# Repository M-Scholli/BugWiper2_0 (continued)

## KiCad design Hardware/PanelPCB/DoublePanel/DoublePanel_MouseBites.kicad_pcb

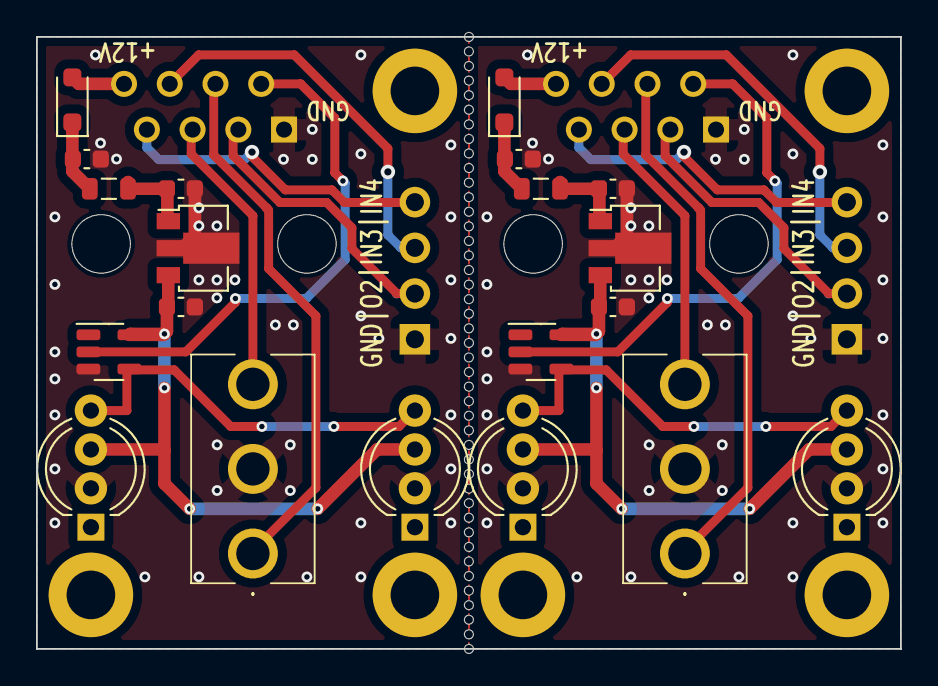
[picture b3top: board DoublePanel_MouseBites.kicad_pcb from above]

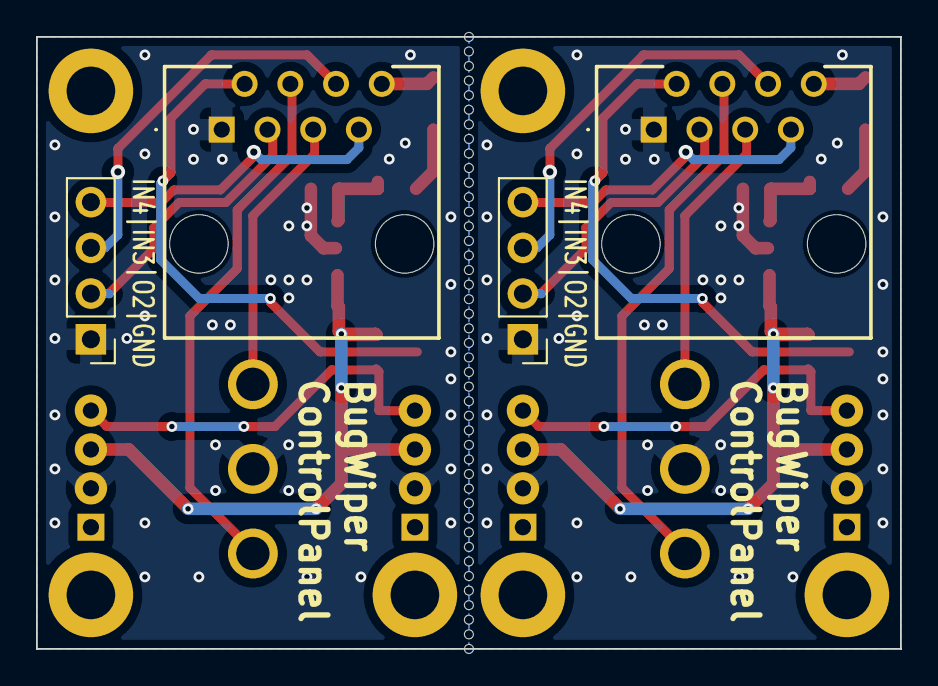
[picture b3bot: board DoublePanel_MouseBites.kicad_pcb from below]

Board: 2 copper layers, 48.0 x 34.0 mm, 73 parts (4 on the bottom side), 24 nets.

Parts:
C1, C1#2, C3, C3#2: 100nF; C_0603_1608Metric
C2, C2#2: 470nF; C_0603_1608Metric
D1, D1#2, D3, D3#2: APA-106-F5; LED_D5.0mm-4_RGB_Wide_Pins
D2, D2#2: CUS15S30,H3F; D_SOD-323_HandSoldering
H1, H1#2, H2, H2#2, H3, H3#2: MountingHole; MountingHole_2.7mm_M2.5_DIN965_Pad
J1, J1#2: RJ45; MJ3415882
J2, J2#2: Conn_01x03_Socket; PinHeader_1x04_P2.54mm_Vertical
KiKit_MB_1_1, KiKit_MB_1_2, KiKit_MB_1_3, KiKit_MB_1_4, KiKit_MB_1_5, KiKit_MB_1_6, KiKit_MB_1_7, KiKit_MB_1_8, KiKit_MB_1_9, KiKit_MB_1_10, KiKit_MB_1_11, KiKit_MB_1_12, KiKit_MB_1_13, KiKit_MB_1_14, KiKit_MB_1_15, KiKit_MB_1_16, KiKit_MB_1_17, KiKit_MB_1_18, KiKit_MB_1_19, KiKit_MB_1_20, KiKit_MB_1_21, KiKit_MB_1_22, KiKit_MB_1_23, KiKit_MB_1_24, KiKit_MB_1_25, KiKit_MB_1_26, KiKit_MB_1_27, KiKit_MB_1_28, KiKit_MB_1_29, KiKit_MB_1_30, KiKit_MB_1_31, KiKit_MB_1_32, KiKit_MB_1_33, KiKit_MB_1_34, KiKit_MB_1_35, KiKit_MB_1_36, KiKit_MB_1_37, KiKit_MB_1_38, KiKit_MB_1_39, KiKit_MB_1_40, KiKit_MB_1_41, KiKit_MB_1_42, KiKit_MB_1_43: NPTH
L1, L1#2: L_Ferrite; L_0805_2012Metric
S1, S1#2: 100SP4T1B4M2QE
U1, U1#2: AP2204R-5.0; SOT-89-3
U2, U2#2: SN74LV1T34DBV; SOT-23-5

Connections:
Board_0-+5V: C2#2.1, D1.3 (VDD), D3.3 (VDD), U1#2.3 (VOUT), U2#2.5 (VCC)
Board_0-GND1: C1#2.2, C2#2.2, C3.2, D1.2 (GND), D3.2 (GND), J1.1, J2.1, S1.2 (COM), U1#2.2 (GND), U2#2.3 (GND)
Board_0-IN1: J1.4, S1.1 (NO)
Board_0-IN2: J1.5, S1.3 (NO)
Board_0-IN3: J1.6, J2.3
Board_0-IN4: J1.7, J2.4
Board_0-Net-(D2-K): C3.1, D2#2.1 (K), L1#2.1
Board_0-Net-(U1-VIN): C1#2.1, L1#2.2, U1#2.1 (VIN)
Board_0-OUT1: J1.2, U2#2.2 (A)
Board_0-OUT2: J1.3, J2.2
Board_0-OUT_1: D1.4 (DI), D3.4 (DI), U2#2.4 (Y)
Board_0-V_IN: D2#2.2 (A), J1.8
Board_1-+5V: C2.1, D1#2.3 (VDD), D3#2.3 (VDD), U1.3 (VOUT), U2.5 (VCC)
Board_1-GND1: C1.2, C2.2, C3#2.2, D1#2.2 (GND), D3#2.2 (GND), J1#2.1, J2#2.1, S1#2.2 (COM), U1.2 (GND), U2.3 (GND)
Board_1-IN1: J1#2.4, S1#2.1 (NO)
Board_1-IN2: J1#2.5, S1#2.3 (NO)
Board_1-IN3: J1#2.6, J2#2.3
Board_1-IN4: J1#2.7, J2#2.4
Board_1-Net-(D2-K): C3#2.1, D2.1 (K), L1.1
Board_1-Net-(U1-VIN): C1.1, L1.2, U1.1 (VIN)
Board_1-OUT1: J1#2.2, U2.2 (A)
Board_1-OUT2: J1#2.3, J2#2.2
Board_1-OUT_1: D1#2.4 (DI), D3#2.4 (DI), U2.4 (Y)
Board_1-V_IN: D2.2 (A), J1#2.8

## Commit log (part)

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2016-07-02 Auskommentierter Code gelöscht
2016-07-02 Benutzung der Arduino PWM Befehle
2016-07-02 überflüssige Funktionen gelöscht und den Definitionsteil neu formatiert
2016-07-02 Sicherheit Taster ( SAVE_PIN) wird jetzt in der Main abgefragt und wird mit der Arduino Lib abgefragt.
2016-07-02 Formatierung und löschen unbenutzter Zeilen
2016-07-02 hinzufügen der Einstellungen von Eclipse
2016-07-02 motor_soft_a gelöscht, da überflüssig
2016-07-02 _delay_ms mit delay ersetzt
2016-07-02 Neue Entprellung ohne Verwendung von Timern oder Interrupts
2016-07-02 Struktur von putzen angepasst und den Lose Taster mit eingebunden
2016-07-04 Es reicht beim Starten die Richtung aus dem EEPROM zu lesen
2016-07-04 neue status anzeige ersetzt erstmal die Tasterreset anzeige, und ist eine Vorbereitung um putzen und einziehen in den loop() zu integrieren um später einen zweiten motor parallel und unabhängig anste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
2016-07-04 in Putzen wir run und safe von putzen_status_a abgelöst
2016-07-04 t_led_a, t_m_pwm_a und t_p_start werden zu globalen variablen gemacht
2016-07-04 putzen Status wird nur zurückgesetzt wenn er vorher 3 ist
2016-07-04 verschieben der Anfangsphase von putzen und einziehen in den Main Loop()
2016-07-04 Funktion Putzen und einziehen wird in die Loop() übertragen
2016-07-04 Umbenennung der Definitionen zur Vorbereitung auf einen zweiten Motor
2016-07-04 Umbenennung der LED zur Vorbereitung auf zweite LED
2016-07-04 Umbenennung von F_FEST_Pin
2016-07-04 Umbenennung von Putzen_PIN und EIn_Ziehen_PIN zur Vorbereitung auf zweiten Motor
2016-07-09 Initialisierung der Ein und Ausgänge der zweiten Motorsteuerung
2016-07-09 Umbenennung der Funktionen und variablen zu .._A um Verwechslungen mit dem zweiten Motor zu verhindern
2016-07-09 hinzufügen der Funktion set_motorpower_b
2016-07-09 die Funktion lese_richtung liest jetzt auch die Richtung des Motors B aus dem EEPROM
2016-07-09 hinzufügen der Funktion aendere_richtung_B
2016-07-09 hinzufügen von stop_B
2016-07-09 Vorbereitungen um die stop Funktionen in die Loop() zu integrieren
2016-07-10 change putzen und einziehen Pin von motor B um die serielle Schnittstelle zum Debuggen benutzen zu können
2016-07-10 Ausgabe des verfügbaren RAMs per RS232
2016-07-10 add to git ignore
2016-07-10 nach Abbrechen des Einziehvorganges wird jetzt die Warnungs-LED angeschaltet
2016-07-10 Auslagern der Tasterabfrage
2016-07-10 weiteres Auslagern nach tasterAbfrage()
2016-07-10 t_taster_lang wird jetzt mit den anderen Zeitzählern im 1ms Takt in setTimer() hochgezählt
2016-07-10 Formatierung
2016-07-10 Auslagern in check_Ende();
2016-07-10 der Aufruf von set_motorpower läuft jetzt zusammen über die selbe if Abfrage
2016-07-12 Belegung der Stecker hinzugefügt
2016-07-16 ändere Status des Lose Pins
2016-07-16 Ausgabe der Motorpower und des Putzstatus
2016-07-16 verlängern des Ausgabezykluszeit und Ausgabe der t_p_start Zeiten
2016-07-16 Entstörung der Taster über Bildung einer Art Mittelwertes. So werden keine Taster mehr ungewollt ausgelöst durch Störungen des Motors oder des Motor PWM Signals. Zudem wurde die PWM Frequenz halbiert.
2016-07-16 durch gedrückt halten des Tasters mit dem der Putz oder Einziehvorgang gestartet wurde, wird der Motor zwangsgefahren, ohne das Sicherheitsfunktionen ihn abschalten können
2016-07-16 Nach dem das Seil wieder stramm ist , startet das PWM signal bei 70 statt bei 0
2016-07-24 Der Motor wird jetzt abgebremst, wenn das Seil lose ist, anstelle nur Stromlos geschaltet zu werden.
2016-07-26 Fehlerbehebung die der Seil Lose Erkennung
2024-02-11 rename file for arduino IDE. change PWM to ESPrename file for arduino IDE. change PWM to ESP32. change Pins to ESP3232. change Pins to ESP32
2024-02-12 change function names. define one or dual motor version
2024-02-12 add serial debug output. change GPI Pins to fix restart and pwm init problem
2024-02-12 move Arduino Code to Software folder
2024-02-12 move documentation of the ESP32 Module to ESP32_docu
2024-02-13 Chane Pin definition
2024-02-13 debug info for starting braking, cleaning and winding in
2024-02-13 move definition
2024-02-13 debug info if cable loose
2024-02-13 ADC to read motor current
2024-02-18 add a encoder to the motor
2024-02-18 change PINs, remove tight switch, add encoder to motor b
2024-02-24 change state machine to switch case version
2024-02-24 fix previous comment and delete eeprom and direction change
2024-02-24 move check_end to state_machines
2024-03-23 Move the BugWiper functions in a class and to file BugWiper.cpp
2024-04-26 use enum for motor direction
2024-04-28 new state machine for the BugWiper. new tranforation of the motorencoder to the position in mm
2024-06-24 add web server with access point to upload config files and download log files in the future
2024-07-30 update webserver for updates and FATFS
2024-12-05 add Pinout picture
2024-12-05 untested changes
2024-12-05 add fotos of the old version
2025-01-02 Remove dualmotor support
2025-01-02 option to exclude the WIFI from compilation
2025-01-02 update readme for the other ESP32 controller board
2025-01-02 move functions to wifi_function.ino
2025-01-02 add init_FAT function
2025-01-02 Disable WIFI for faster development
2025-01-02 update settings to FAT
2025-01-02 fix type
2025-01-02 add pin definition for ESP32-S3
2025-01-03 slow down the serial output in main loop
2025-01-03 move calculation to main and fix devide by zero
2025-01-04 add new motors to the motor calculation.csv
2025-01-07 update motor comparison
2025-01-07 update docs
2025-01-09 Add USB-C and Buttons to the Schematics, PCB and BOM
2025-01-13 update KiCAD files
2025-01-15 Update PCB
2025-01-17 add ESD protection to inputs
2025-01-18 add resistor arrays
2025-01-19 add connector to lib
2025-01-19 update PCB, routing and Connector
2025-01-20 routing
2025-01-21 PCB mostly finished
2025-01-22 Update PCB
    add Connector for Sw_2, add voltage devider for the encoder
2025-01-26 rename PCB folder
2025-01-27 Add a micro SD Card slot to the bottom of the controller board
2025-01-27 export schematics as PDF
2025-01-27 Export schematics
2025-01-28 update Controller PCB
    Add Fuses for GND Signal Connectors, fix 3D and fix DRC
2025-01-29 Update PCB
    Add solder jumper for +3.3V selection
    fix DRC
    aligne vias
    export Gerber
    add text
    fix 3D Models
2025-01-30 update Controller PCB
    Add additional capacitor
    fix footprint Resistor Array CAT16
    fix 3D Model CAT16
    change traces from 0.5 to 0.4 mm
    fix USB-C Footprint
    Export Gerber
2025-01-30 update PanelPCB and generade a DualPanelPCB
2025-02-04 update PCB and Gerber
    change Switches to cheaper ones
2025-02-24 update Controller PCB PDF Export and layer of Values and Reference
2025-02-26 Export PCBs as Step and start CAD construction
2025-02-26 update CAD Modell
2025-05-10 export PDF with dimension of the PCB
2025-05-10 update motor CAD model
2025-05-18 update gitignore
2025-05-18 add debug infos via macros
2025-05-18 go back to c function for the bugwiper
2025-05-18 initialise LED and Motor pins
2025-05-19 change debug info
2025-05-19 change debug infos
2025-05-19 implement btn99xx motor controller and test function for the Motor.
2025-05-19 update lib
2025-05-20 clean code
2025-05-20 add more debug infos
2025-05-20 spoole housig is finished and ready for export
2025-05-21 update CAD Model and export stl
2025-05-22 read buttons. implements two tasks for the BugWiper system
2025-05-22 update CAD
2025-05-22 add Fotos to place inserts
2025-05-22 write modes and LED colour, stop when pressing the switch in the other direction
2025-05-22 fix state machine
2025-05-23 read more ADCs for DEBUG infos
2025-05-23 fixes
2025-05-23 calib ADC
2025-05-23 read ADCs and check for undervoltage and overtemperature
2025-05-23 change settings for testbench and add debug infos
2025-05-24 add second state machine timer to brake and pause the motot at the wingtip to prevent high current spikes when changing the direction
2025-05-24 move the read encoder function to a slower task to get higher speed values
2025-05-24 implement an rolling average filter for the ADC motor current
2025-05-24 optimise parameter and add a minimal cleaning time for winding in
2025-05-24 speed must be below minimum twenty times in a rom to stop the motor
2025-05-25 version 2 of CAD model
2025-05-25 deflection pulley for the bowden tube
2025-06-02 fix fillet radius of the cover, add bigger pocket for the connector of the switch
2025-06-02 fix hole size and position
2025-06-02 update controller PCB: change Encoder filter to 1nF add 0 Ohm resistor for JP1 to BOM
2025-06-03 fix motorhousing2
2025-11-11 fix empty stl files
2025-11-11 update CAD Model and export Housing as stl
2026-04-18 update to FreeCad 1.1 and add slots for screw of the motor housing
2026-04-18 add a slot for the micro sd kart to the motor housing
2026-04-18 Add SD Card logging to the bugwiper
2026-04-18 Change LED colours and remove LED test at start
2026-04-19 create two funktions for logging data. Add logging to all state changes in the state machine.
2026-04-19 change parameters
2026-04-24 Update documentation
2026-04-28 fsm: refactor motor control and FSM entry actions (WIP)
    Refactors motor control to separate FSM intent from motor runtime
    using MotorCommand and MotorState. Mode configuration and FSM entry
    logic updated accordingly.
    Builds successfully, but state logic is not yet complete
2026-04-30 Update README.md to fix broken links
2026-05-01 Refactor BugWiper codebase for consistency and clarity by renaming functions and variables, updating logging methods, and consolidating threshold definitions.
2026-05-01 Refactor BugWiper code to enhance button handling and filtering mechanisms, introducing BwFilter and ButtonRuntime structures for improved state management and debounce logic.
2026-05-03 Increase stack size for BugWiper_Task1_fast to prevent Stack-Overflow
2026-05-03 Update BugWiperSystem_Bambu.3mf file for improved housing design
2026-05-03 Reset lastUserCommand to CMD_NONE in stateFinished, stateStop, and stateError functions for improved state management
2026-05-03 Change default next mode to M_REFERENCE_IN in stateIdle function for improved state transition
2026-05-03 Enable cable loose switch inversion
2026-05-03 Refactor button logging functions for improved clarity and maintainability
2026-05-03 Update motor configuration parameters and refactor ramp time handling
2026-05-03 Refactor encoder handling: consolidate encoder reset logic , improve reading function and add reset function
2026-05-03 Update motor stop thresholds and refine start power settings for improved control
2026-05-03 Update PCB files and documentation for BugWiper 2.0: change revision to V1.2, update value from C4 from 100nF to 470nF
2026-05-04 Update default next mode to CLEANING for improved workflow after loose detection
2026-05-04 Refactor stateWindingIn function to remove timeout logic and simplify implementation
2026-05-04 Fix typos in comments for clarity and consistency
2026-05-05 optimize wiggle parameters
2026-05-05 fix transition conditions from WindingIn to WindingInDecel
2026-05-06 update PCB test
2026-05-06 add Task execution time to debug infos
2026-05-06 add global WingTipCheck
2026-05-06 update prototype tests
2026-05-09 update prototype list
2026-05-09 deactivate Testbench
2026-05-09 show ground switch state at init
2026-05-09 activate Ground Mode
2026-05-09 add debug infos groundmode
2026-05-09 change blinkTimes
2026-05-09 update sw version
2026-05-09 fix Ground Mode
2026-05-09 update defines
2026-05-09 update config
2026-05-09 config changes
2026-05-09 remove unused parameter
2026-05-11 redesign wiggle in and out
2026-05-11 usw commas to separate columns in csv file
2026-05-11 no bw_log at setup()
2026-05-11 do not write logfile bevor start of cleaning or winding in
2026-05-11 optimize setup() and split initSD() to save time
2026-05-11 write events to sd card
2026-05-11 fix sdLoggerHandleCard()
2026-05-11 change wiggle timeout
2026-05-11 change debug level for task time
2026-05-11 optimize wiggle algorithm
2026-05-11 change motorSlowedDown() to last order in if statement to reduce logging events
2026-05-29 update and refractor the documentation
2026-05-29 refractor flight tests and upload more logfiles
2026-05-29 plot flight logs from 2026-05-15
